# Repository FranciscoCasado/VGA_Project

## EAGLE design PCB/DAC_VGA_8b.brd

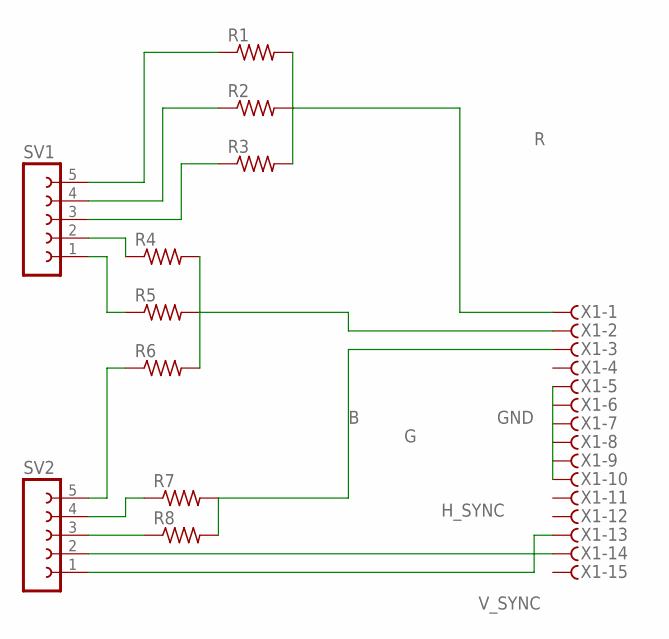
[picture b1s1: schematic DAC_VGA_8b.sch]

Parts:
R1, R2, R3, R4, R5, R6, R7, R8: R-US_0204/5; 0204/5
SV1, SV2: FE05W
X1: HF15VS; HDF15V

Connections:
B: R7.2, R8.2, X1.3
G: R4.2, R5.2, R6.2, X1.2
GND: X1.5, X1.6, X1.7, X1.8, X1.9, X1.10
H_SYNC: SV2.2, X1.14
unnamed: R4.1, SV1.2
unnamed: R5.1, SV1.1
unnamed: R6.1, SV2.5
unnamed: R7.1, SV2.4
unnamed: R8.1, SV2.3
unnamed: R3.1, SV1.3
unnamed: R2.1, SV1.4
unnamed: R1.1, SV1.5
R: R1.2, R2.2, R3.2, X1.1
V_SYNC: SV2.1, X1.13

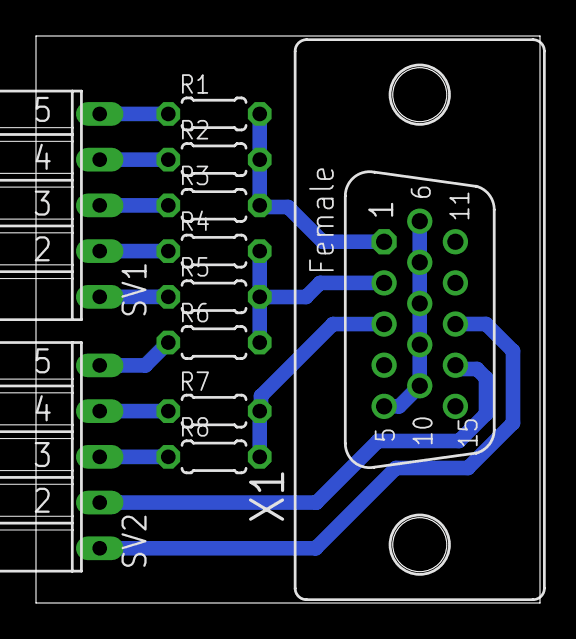
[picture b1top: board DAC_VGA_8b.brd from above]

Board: 2 copper layers, 28.0 x 31.5 mm, 11 parts (0 on the bottom side), 14 nets.

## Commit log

2015-06-03 Simple VGA Display
2015-06-04 Simple Image to Vga Project added. Also parser and coe tools were added
2015-06-04 Fixed radix in matlab script
2015-06-04 Memory interface works, displays image in 8 bits
2015-06-04 Some project files were deleted. Nothing to worry about
2015-06-08 Palette almost working red and blue seems fine. green sucks
2015-06-09 256 palette generated in verilog seems fine. Left to test in proper board
2015-06-09 Channels red and blue are working properly. Green channel sucks. Palette image generated with matlab used as memory
2015-06-09 Propuesta inicial para pre entrega
2015-06-09 Initial Pong Game. Wont Work
2015-06-09 Palette WORKS ! ! !
2015-06-09 Add Nyan_0 frame
2015-06-09 FranciscCasado
2015-06-10 EAGLE file for PCB printing
2015-06-24 Dont know what i´m doin´
2015-06-24 Working fine
2015-06-24 Again (?)
2015-06-24 Deleted build files.
2015-06-24 Deleted build files from PreEntrega8Bits
2015-06-24 Deleted build files from PaletteDisplay256
2015-06-24 Deleted build files from PaintVGA.
2015-06-24 Deleted more build files from PaintVGA
2015-06-24 Deleted build files from SimpleVGADisplay.
2015-06-24 Deleted build files from SimpleImage2VGA.
2015-06-24 Updated and refactored Tools.
2015-06-24 Added a binaries folder, just as a failsafe.
2015-06-24 Added project PaletteDisplay256-2.
2015-06-24 Added project PongVGA2. Player dynamics work fine. Ball is left.
2015-06-24 Added ball dynamics. Works fine.
2015-06-24 Can display numbers, but must invert them... my bad.
2015-06-24 Now Displays numbers correctly.
2015-06-24 Displays Score OK
2015-06-24 Added reset. Score 2 was fixed.
2015-06-24 Added PongVGA2 bin.
2015-06-24 Fixed bin.
2015-06-25 Added gif bin.
